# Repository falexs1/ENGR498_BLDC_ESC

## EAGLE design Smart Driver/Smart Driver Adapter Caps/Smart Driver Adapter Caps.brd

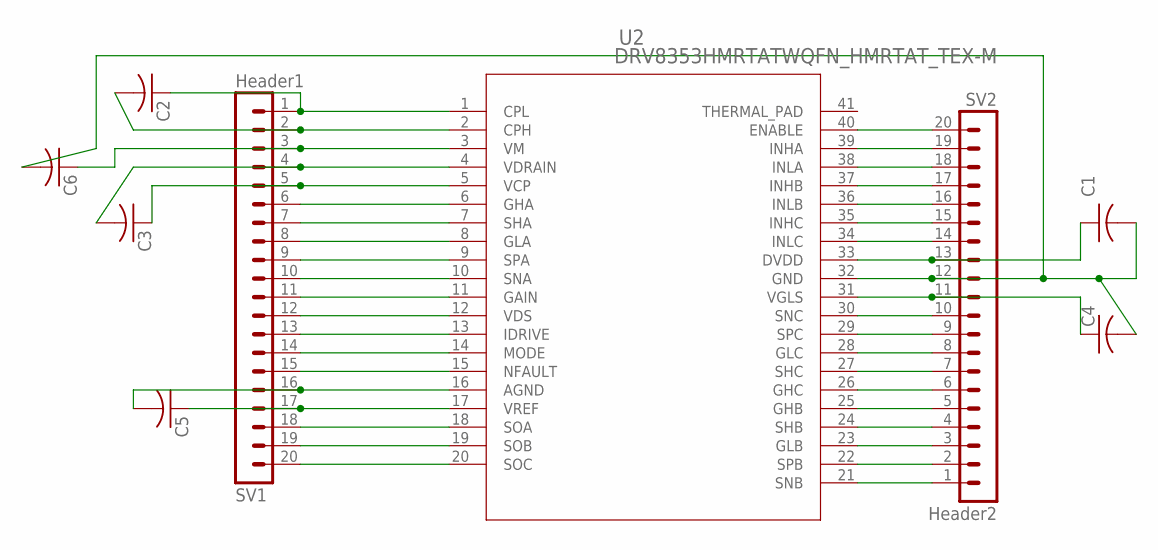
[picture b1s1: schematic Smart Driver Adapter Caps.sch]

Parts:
C1: C-USC0603K; C0603K
C2, C6: C-USC1206K; C1206K
C3, C4: C-USC0805K; C0805K
C5: C-USC0201; C0201
SV1: Header1; MA20-1
SV2: Header2; MA20-1
U2: DRV8353HMRTATWQFN_HMRTAT_TEX-M; WQFN_HMRTAT_TEX-M

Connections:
unnamed: C1.1, SV2.13, U2.33 (DVDD)
unnamed: SV1.14, U2.14 (MODE)
unnamed: C2.2, SV1.2, U2.2 (CPH)
unnamed: C6.1, SV1.3, U2.3 (VM)
unnamed: C3.1, SV1.5, U2.5 (VCP)
unnamed: SV1.6, U2.6 (GHA)
unnamed: SV1.7, U2.7 (SHA)
unnamed: SV1.8, U2.8 (GLA)
unnamed: SV1.9, U2.9 (SPA)
unnamed: SV1.10, U2.10 (SNA)
unnamed: SV1.11, U2.11 (GAIN)
unnamed: SV1.13, U2.13 (IDRIVE)
unnamed: SV1.15, U2.15 (NFAULT)
unnamed: C5.1, SV1.17, U2.17 (VREF)
unnamed: C4.1, SV2.11, U2.31 (VGLS)
unnamed: SV1.18, U2.18 (SOA)
unnamed: SV1.20, U2.20 (SOC)
unnamed: SV2.20, U2.40 (ENABLE)
unnamed: SV2.19, U2.39 (INHA)
unnamed: SV2.18, U2.38 (INLA)
unnamed: SV2.17, U2.37 (INHB)
unnamed: SV2.16, U2.36 (INLB)
unnamed: SV2.15, U2.35 (INHC)
unnamed: SV2.14, U2.34 (INLC)
unnamed: C5.2, SV1.16, U2.16 (AGND)
unnamed: C1.2, C4.2, C6.2, SV2.12, U2.32 (GND)
unnamed: C2.1, SV1.1, U2.1 (CPL)
unnamed: SV2.10, U2.30 (SNC)
unnamed: SV2.9, U2.29 (SPC)
unnamed: SV2.8, U2.28 (GLC)
unnamed: SV2.7, U2.27 (SHC)
unnamed: SV2.6, U2.26 (GHC)
unnamed: SV2.5, U2.25 (GHB)
unnamed: SV2.4, U2.24 (SHB)
unnamed: SV2.3, U2.23 (GLB)
unnamed: SV2.2, U2.22 (SPB)
unnamed: SV2.1, U2.21 (SNB)
unnamed: SV1.12, U2.12 (VDS)
unnamed: SV1.19, U2.19 (SOB)
unnamed: C3.2, SV1.4, U2.4 (VDRAIN)

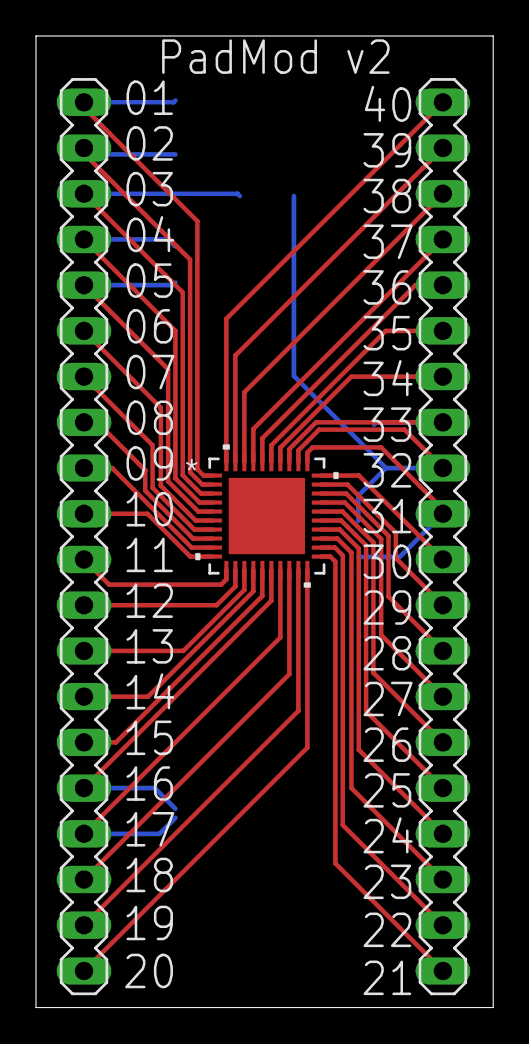
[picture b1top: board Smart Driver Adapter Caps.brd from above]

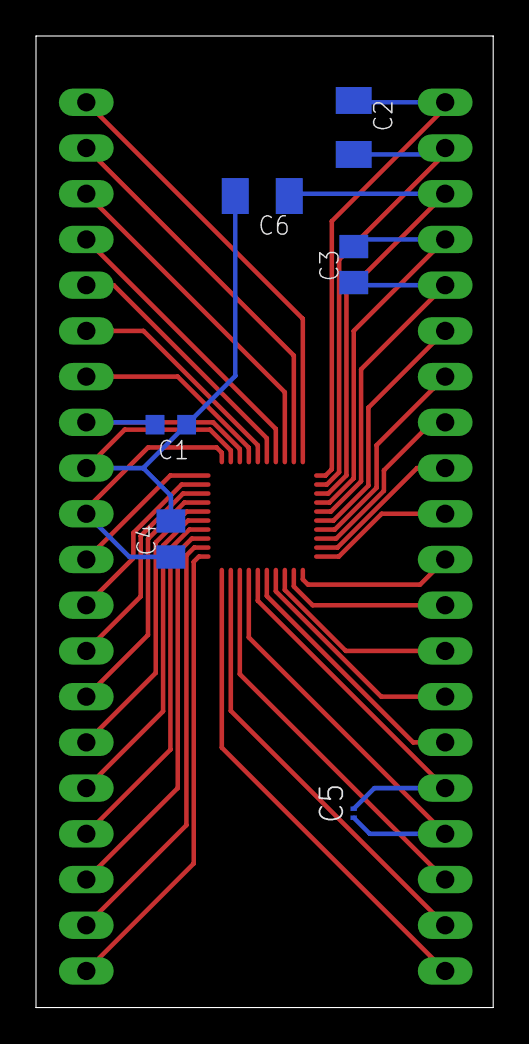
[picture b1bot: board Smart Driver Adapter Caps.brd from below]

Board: 2 copper layers, 25.4 x 54.0 mm, 9 parts (6 on the bottom side), 40 nets.

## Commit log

2022-02-24 Repo Creation
2022-02-24 Removed Dup Adapter
2022-02-24 Git Ignore Updated
2022-02-24 Cleaning
2022-02-24 GitIgnore
2022-02-24 version 2
    i dont know if this is the right thing i dont know how to check fuck me
2022-02-24 Correcting PadMod Version of PCB
2022-02-24 Modified text on PCB
2022-02-24 Corrected Adapter with Caps PCB
2022-02-24 Created CAM files for manufacturing
2022-02-24 Restructure
2022-02-24 Revert "Restructure"
    This reverts commit f01694b5691f11728d20e49bc872cf853cd4a49f.
2022-02-25 TEST
2022-02-25 Renamed Code Folder
2022-02-25 Code Folder

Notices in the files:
parts and their libraries:
COPYRIGHT: Copyright (C) 2021 Ultra Librarian. All rights reserved.
